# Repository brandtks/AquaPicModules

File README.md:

README
======
Board design and firmware for all modules used with the AquaPic Aquarium Controller. Each board should have corresponding firmware that works with that board version. All modules communicate with and are controlled by the [master controller/head unit](https://github.com/AquaPic/AquaPicController).

 * All PCB designs and layouts including gerber files are located under the _Boards_ directory. All PCB design is done using [KiCAD](http://kicad-pcb.org/). 
 * Firmware is located in the _Firmware_ directory. All the card's firmware should build without the need of the [MPLAB X IDE](http://www.microchip.com/mplab/mplab-x-ide), just the [XC compilers](http://www.microchip.com/mplab/compilers).
 * The _Documentation_ directory contains some useful information such as AquaPic Bus packets and other random notes.
 * Bill of materials are shared in [Google Drive](https://drive.google.com/drive/folders/1AOH0jgJ0CXvZnuD189EO4B9ZkvwggwkB?usp=sharing). 

### Status 
**IMPORTANT**: All modules are a work in progress. Most, if not all, are untested and very alpha quality.

### Website 
[HackADay Build Log](https://hackaday.io/project/1436-aquapic-aquarium-controller)

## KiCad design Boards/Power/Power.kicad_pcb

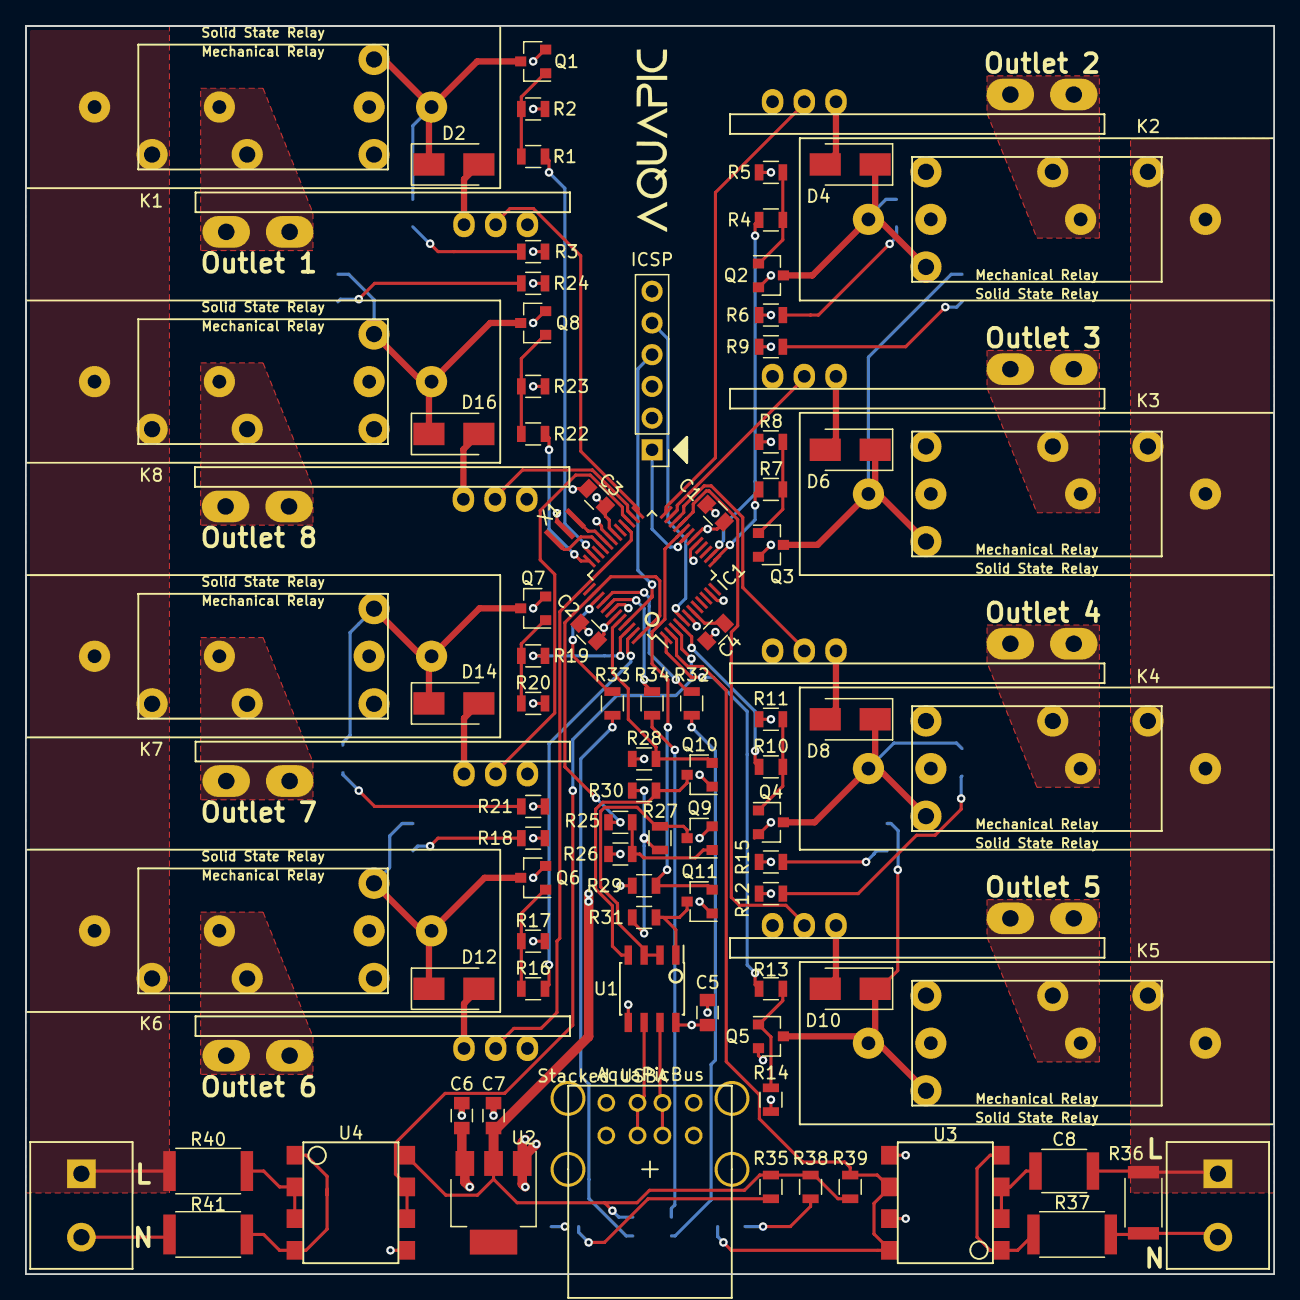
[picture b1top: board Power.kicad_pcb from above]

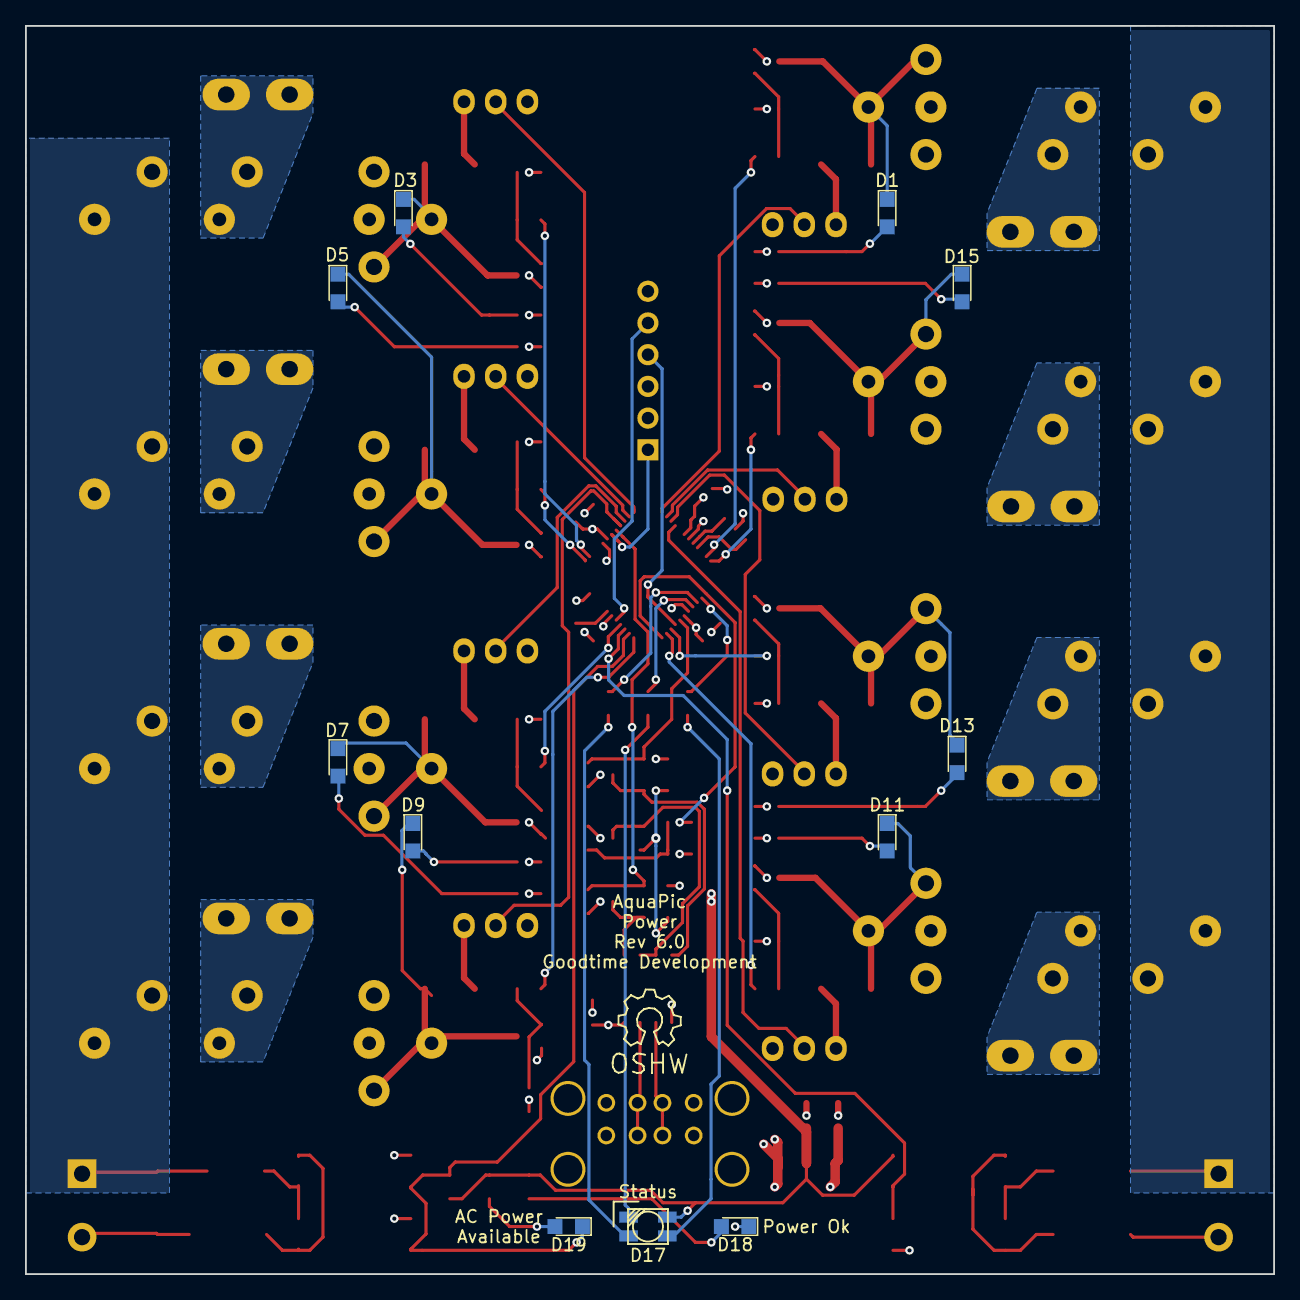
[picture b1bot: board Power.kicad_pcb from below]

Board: 4 copper layers, 100.0 x 100.0 mm, 105 parts (11 on the bottom side), 82 nets.

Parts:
C1, C2, C3, C4, C5: 100nF; C_0805
C6, C7: 4u7; C_0805
C8: 470nF; C_1812
D1, D3, D5, D7, D9, D11, D13, D15, D18, D19: APT2012; LED_0805
D2, D4, D6, D8, D10, D12, D14, D16: STPS130A; D_SMA
D17: SMTL4-RGY; PLCC-4
IC1: PIC32MM0064GPM048; TQFP-48_7x7mm_Pitch0.5mm
ICSP: 1x6 2.54 Pin Header; Pin_Header_Straight_1x06_Pitch2.54mm
K1, K2, K3, K4, K5, K6, K7, K8: Relay(Mech/SSR); Relay-Mech-SSR
P1, P2, P3, P4, P5, P6, P7, P8: Stab and 1x3; Current_Board
P11: Stacked USBA; USB-1.1_Stacked
P12, P13: 1x2 5.08; Screw_Header_1x2_5.08
Q1, Q2, Q3, Q4, Q5, Q6, Q7, Q8, Q9, Q10, Q11: NX7002AK; SOT-23
R1, R4, R7, R10, R13, R16, R19, R22, R25: 1K; R_0805
R2, R5, R8, R11, R14, R17, R20, R23, R26, R27, R39: 10K; R_0805
R3, R6, R9, R12, R15, R18, R21, R24: 100R; R_0805
R28, R29, R30, R31: 4K99; R_0805
R32, R33, R34, R35, R38: 150R; R_0805
R36: 1M; R_2010
R37: 1K; R_2512
R40, R41: 13K; R_2512
U1: ST485EC; SOIC-8_3.9x4.9mm_Pitch1.27mm
U2: AP2114H; SOT-223
U3, U4: LTV-826; 8_SMD_GULL_WING
X1: 8MHz; Resonator_3.2x1.3

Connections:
+3V3: C1.1, C2.1, C3.1, C7.1, D17.4, IC1.18, IC1.30, IC1.43, ICSP.2, Q10.1, Q11.1, R28.1, R29.1, R35.1, R38.2, R39.1, U2.2, U4.8
+5V: C5.1, C6.1, D2.2, D4.2, D6.2, D8.2, D10.2, D12.2, D14.2, D16.2, K1.3-1, K1.3-2, K2.3-1, K2.3-2, K3.3-1, K3.3-2, K4.3-1, K4.3-2, K5.3-1, K5.3-2, K6.3-1, K6.3-2, K7.3-1, K7.3-2, K8.3-1, K8.3-2, P1.2, P2.2, P3.2, P4.2, P5.2, P6.2, P7.2, P8.2, P11.1, P11.5, R3.1, R6.1, R9.1, R12.1, R15.1, R18.1, R21.1, R24.1, R27.1, R30.1, R31.1, U1.8, U2.3
//MCLR: IC1.19, ICSP.1
//RTS: IC1.38, IC1.48, R25.2
/A: P11.2, P11.6, U1.6
/AC_AVAIL: D19.1, IC1.2, R39.2, U3.6, U3.8
/B: P11.3, P11.7, U1.7
/CURRENT_1: IC1.25, P1.3
/CURRENT_2: IC1.24, P2.3
/CURRENT_3: IC1.23, P3.3
/CURRENT_4: IC1.22, P4.3
/CURRENT_5: IC1.21, P5.3
/CURRENT_6: IC1.28, P6.3
/CURRENT_7: IC1.27, P7.3
/CURRENT_8: IC1.26, P8.3
/L: C8.1, K1.1-1, K1.1-2, K2.1-1, K2.1-2, K3.1-1, K3.1-2, K4.1-1, K4.1-2, K5.1-1, K5.1-2, K6.1-1, K6.1-2, K7.1-1, K7.1-2, K8.1-1, K8.1-2, P12.1, P13.1, R36.2, R40.2
/L1: K1.2-1, K1.2-2, P1.1
/L2: K2.2-1, K2.2-2, P2.1
/L3: K3.2-1, K3.2-2, P3.1
/L4: K4.2-1, K4.2-2, P4.1
/L5: K5.2-1, K5.2-2, P5.1
/L6: K6.2-1, K6.2-2, P6.1
/L7: K7.2-1, K7.2-2, P7.1
/L8: K8.2-1, K8.2-2, P8.1
/LED_G: IC1.40, R32.2
/LED_R: IC1.41, R34.2
/LED_Y: IC1.39, R33.2
/N: P12.2, P13.2, R36.1, R37.1, R41.2
/PGC: IC1.5, ICSP.5
/PGD: IC1.45, ICSP.4
/RELAY_1: IC1.35, R1.2
/RELAY_2: IC1.14, R4.2
/RELAY_3: IC1.13, R7.2
/RELAY_4: IC1.4, R10.2
/RELAY_5: IC1.1, R13.2
/RELAY_6: IC1.47, R16.2
/RELAY_7: IC1.46, R19.2
/RELAY_8: IC1.36, R22.2
/RTS: Q9.3, R27.2, U1.2, U1.3
/RX: Q11.3, R31.2, U1.1
/RX_LV: IC1.20, Q11.2, R29.2
/TX: Q10.3, R30.2, U1.4
/TX_LV: IC1.44, Q10.2, R28.2
/ZERO_CROSS: IC1.3, U4.6, U4.7
GND: C1.2, C2.2, C3.2, C4.2, C5.2, C6.2, C7.2, D18.1, IC1.6, IC1.11, IC1.17, IC1.31, IC1.42, ICSP.3, P1.4, P2.4, P3.4, P4.4, P5.4, P6.4, P7.4, P8.4, P11.4, P11.8, Q1.2, Q2.2, Q3.2, Q4.2, Q5.2, Q6.2, Q7.2, Q8.2, Q9.2, R2.2, R5.2, R8.2, R11.2, R14.2, R17.2, R20.2, R23.2, R26.2, U1.5, U2.1, U3.5, U3.7, U4.5, X1.2
unnamed: C4.1, IC1.7
unnamed: C8.2, U3.2, U3.3
unnamed: D1.1, D2.1, K1.4-1, K1.4-2, Q1.3
unnamed: D1.2, R3.2
unnamed: D3.1, D4.1, K2.4-1, K2.4-2, Q2.3
unnamed: D3.2, R6.2
unnamed: D5.1, D6.1, K3.4-1, K3.4-2, Q3.3
unnamed: D5.2, R9.2
unnamed: D7.1, D8.1, K4.4-1, K4.4-2, Q4.3
unnamed: D7.2, R12.2
unnamed: D9.2, R15.2
unnamed: D9.1, D10.1, K5.4-1, K5.4-2, Q5.3
unnamed: D11.1, D12.1, K6.4-1, K6.4-2, Q6.3
unnamed: D11.2, R18.2
unnamed: D13.1, D14.1, K7.4-1, K7.4-2, Q7.3
unnamed: D13.2, R21.2
unnamed: D15.1, D16.1, K8.4-1, K8.4-2, Q8.3
unnamed: D15.2, R24.2
unnamed: D17.1, R32.1
unnamed: D17.2, R33.1
unnamed: D17.3, R34.1
unnamed: D18.2, R35.2
unnamed: D19.2, R38.1
unnamed: IC1.32, X1.3
unnamed: IC1.33, X1.1
unnamed: Q1.1, R1.1, R2.1
unnamed: Q2.1, R4.1, R5.1
unnamed: Q3.1, R7.1, R8.1
unnamed: Q4.1, R10.1, R11.1
unnamed: Q5.1, R13.1, R14.1
unnamed: Q6.1, R16.1, R17.1
unnamed: Q7.1, R19.1, R20.1
unnamed: Q8.1, R22.1, R23.1
unnamed: Q9.1, R25.1, R26.1
unnamed: R37.2, U3.1, U3.4
unnamed: R40.1, U4.2, U4.3
unnamed: R41.1, U4.1, U4.4

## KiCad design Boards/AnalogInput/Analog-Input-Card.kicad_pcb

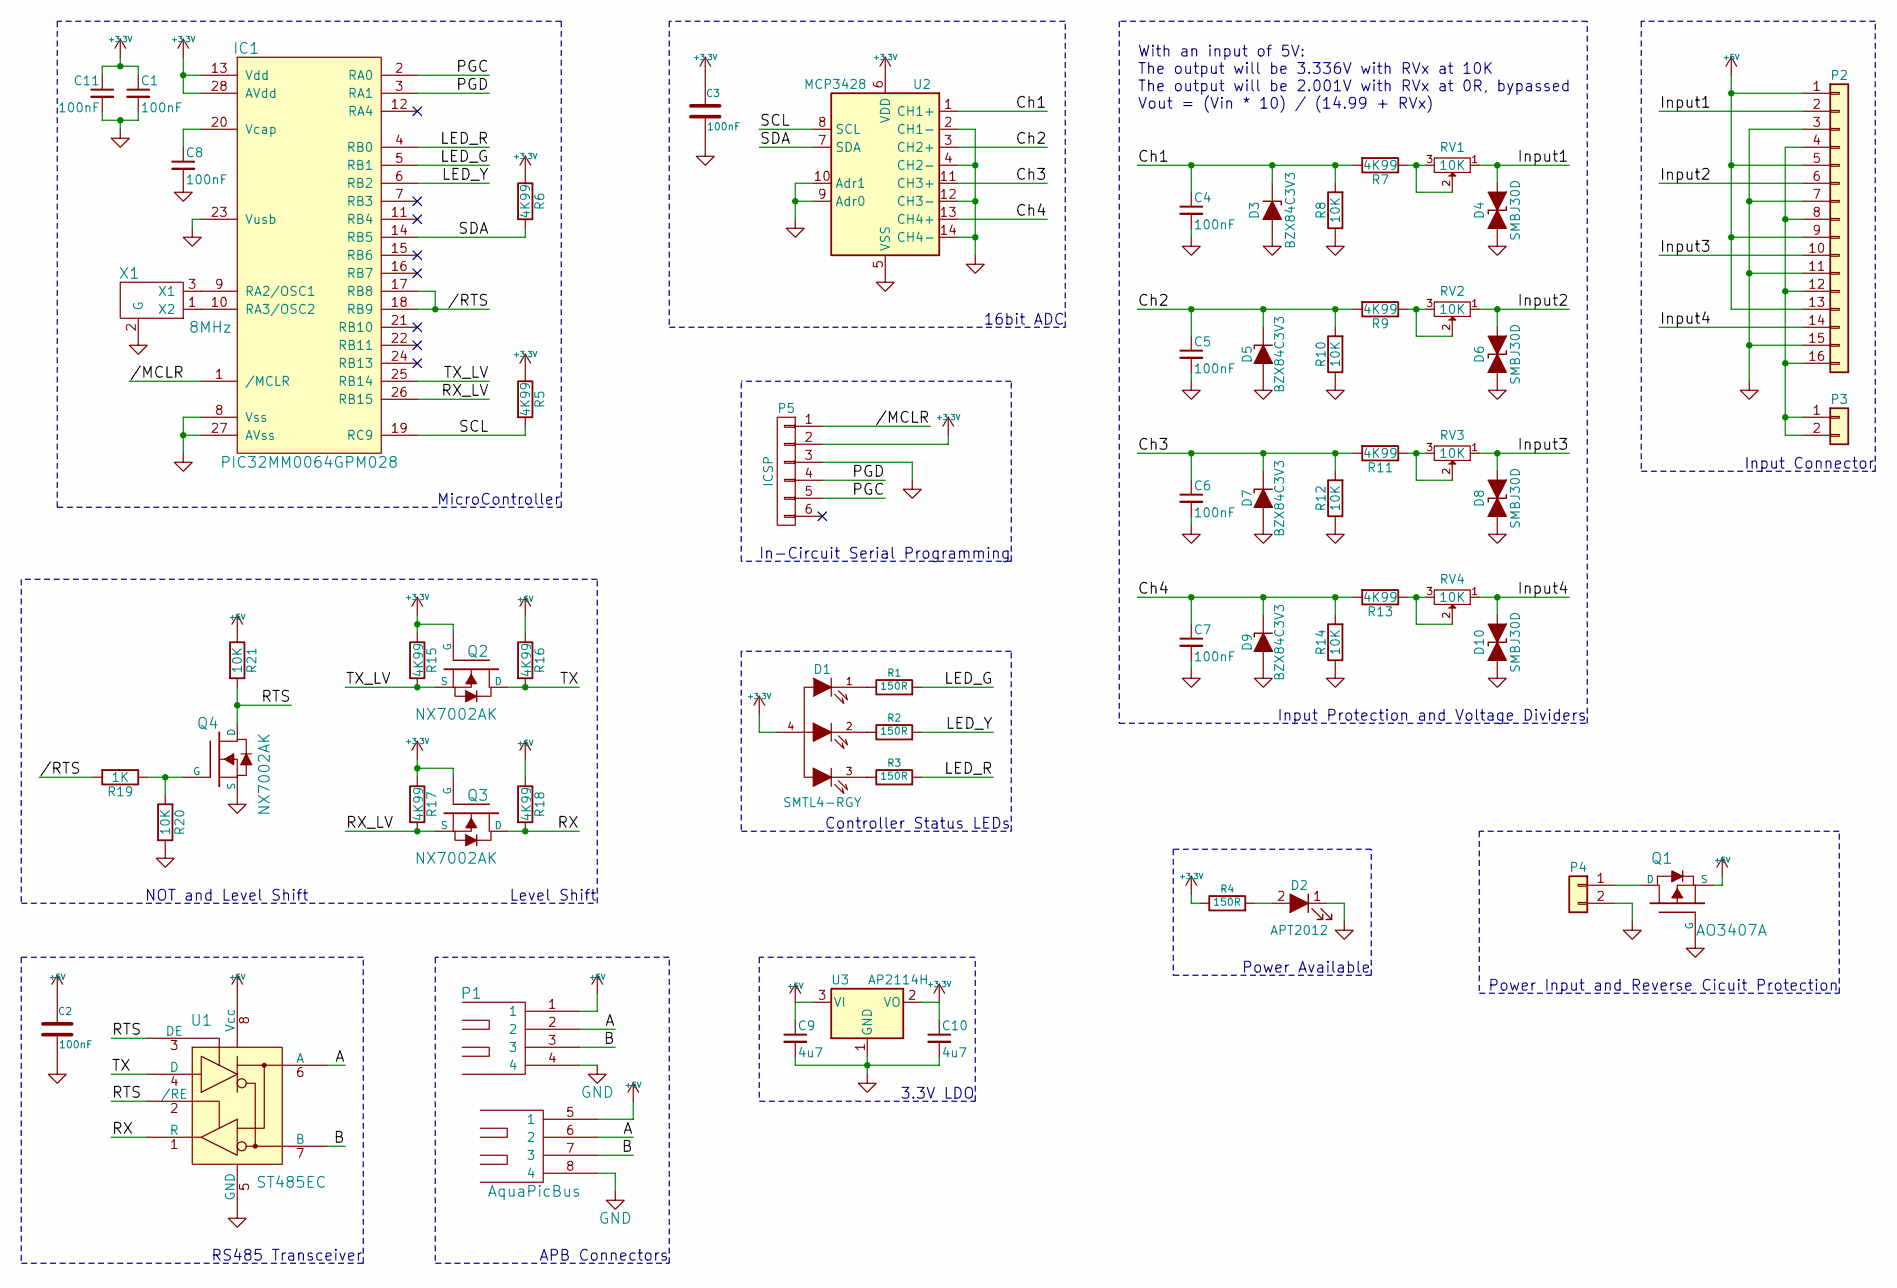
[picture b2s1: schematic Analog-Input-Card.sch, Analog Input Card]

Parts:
C1, C2, C3, C4, C5, C6, C7, C8, C11: 100nF; C_0805
C9, C10: 4u7; C_0805
D1: SMTL4-RGY; PLCC-4
D2: APT2012; LED-0805
D3, D5, D7, D9: BZX84C3V3; D_SOT-23_ANK
D4, D6, D8, D10: SMBJ30D; D_SMB
IC1: PIC32MM0064GPM028; SSOP-28_5.3x10.2mm_Pitch0.65mm
P1: AquaPicBus; USB-1.1_Stacked
P2: 1x16 2.54; Screw_Header_1x16
P3, P4: 1x2 2.54; Screw_Header_1x2
P5: ICSP; Pin_Header_Straight_1x06_Pitch2.54mm
Q1: AO3407A; SOT-23
Q2, Q3, Q4: NX7002AK; SOT-23
R1, R2, R3, R4: 150R; R_0805
R5, R6, R7, R9, R11, R13, R15, R16, R17, R18: 4K99; R_0805
R8, R10, R12, R14, R20, R21: 10K; R_0805
R19: 1K; R_0805
RV1, RV2, RV3, RV4: 10K; POTENTIAMETER_SMD
U1: ST485EC; SOIC-8_3.9x4.9mm_Pitch1.27mm
U2: MCP3428; TSSOP-14_4.4x5mm_Pitch0.65mm
U3: AP2114H; SOT-223
X1: 8MHz; Resonator_3.2x1.3

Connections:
+3V3: C1.1, C3.1, C10.1, C11.1, D1.4, IC1.13 (Vdd), IC1.28 (AVdd), P5.2, Q2.1 (G), Q3.1 (G), R4.1, R5.1, R6.1, R15.1, R17.1, U2.6 (VDD), U3.2 (VO); also elsewhere on the board
+5V: C2.1, C9.1, P1.1, P1.5 (1), P2.1, P2.5, P2.9, P2.13, Q1.2 (S), R16.1, R18.1, R21.1, U1.8 (Vcc), U3.3 (VI)
//MCLR: IC1.1 (/MCLR), P5.1; also elsewhere on the board
//RTS: IC1.17 (RB8), IC1.18 (RB9), R19.2
/A: P1.2, P1.6 (2), U1.6 (A)
/B: P1.3, P1.7 (3), U1.7 (B)
/Ch1: C4.1, D3.1 (K), R7.2, R8.2, U2.1 (CH1+)
/Ch2: C5.1, D5.1 (K), R9.2, R10.2, U2.3 (CH2+)
/Ch3: C6.1, D7.1 (K), R11.2, R12.2, U2.11 (CH3+)
/Ch4: C7.1, D9.1 (K), R13.2, R14.2, U2.13 (CH4+)
/Input1: D4.1 (A1), P2.2, RV1.1
/Input2: D6.1 (A1), P2.6, RV2.1
/Input3: D8.1 (A1), P2.10, RV3.1
/Input4: D10.1 (A1), P2.14, RV4.1
/LED_G: IC1.5 (RB1), R1.2
/LED_R: IC1.4 (RB0), R3.2
/LED_Y: IC1.6 (RB2), R2.2
/PGC: IC1.2 (RA0), P5.5; also elsewhere on the board
/PGD: IC1.3 (RA1), P5.4; also elsewhere on the board
/RTS: Q4.3 (D), R21.2, U1.2 (/RE), U1.3 (DE)
/RX: Q3.3 (D), R18.2, U1.1 (R)
/RX_LV: IC1.26 (RB15), Q3.2 (S), R17.2
/SCL: IC1.19 (RC9), R5.2, U2.8 (SCL)
/SDA: IC1.14 (RB5), R6.2, U2.7 (SDA)
/TX: Q2.3 (D), R16.2, U1.4 (D)
/TX_LV: IC1.25 (RB14), Q2.2 (S), R15.2
GND: C1.2, C2.2, C3.2, C4.2, C5.2, C6.2, C7.2, C8.2, C9.2, C10.2, C11.2, D2.1 (K), D3.2 (A), D4.2 (A2), D5.2 (A), D6.2 (A2), D7.2 (A), D8.2 (A2), D9.2 (A), D10.2 (A2), IC1.8 (Vss), IC1.23 (Vusb), IC1.27 (AVss), P1.4, P1.8 (4), P2.3, P2.7, P2.11, P2.15, P4.2, P5.3, Q1.1 (G), Q4.2 (S), R8.1, R10.1, R12.1, R14.1, R20.2, U1.5 (GND), U2.2 (CH1-), U2.4 (CH2-), U2.5 (VSS), U2.9 (Adr0), U2.10 (Adr1), U2.12 (CH3-), U2.14 (CH4-), U3.1 (GND), X1.2 (G); also elsewhere on the board
unnamed: C8.1, IC1.20 (Vcap)
unnamed: D1.1, R1.1
unnamed: D1.2, R2.1
unnamed: D1.3, R3.1
unnamed: D2.2 (A), R4.2
unnamed: IC1.9 (RA2/OSC1), X1.3 (X1)
unnamed: IC1.10 (RA3/OSC2), X1.1 (X2)
unnamed: P2.4, P2.8, P2.12, P2.16, P3.1, P3.2
unnamed 43: P4.1, Q1.3 (D); also elsewhere on the board
unnamed: Q4.1 (G), R19.1, R20.1
unnamed: R7.1, RV1.2, RV1.3
unnamed: R9.1, RV2.2, RV2.3
unnamed: R11.1, RV3.2, RV3.3
unnamed: R13.1, RV4.2, RV4.3

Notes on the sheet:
In-Circuit Serial Programming
MicroController
Input Connector
RS485 Transceiver
Power Input and Reverse Cicuit Protection
APB Connectors
16bit ADC
Input Protection and Voltage Dividers
With an input of 5V: The output will be 3.336V with RVx at 10K The output will be 2.001V with RVx at 0R, bypassed Vout = (Vin * 10) / (14.99 + RVx)
Level Shift
NOT and Level Shift
3.3V LDO
Controller Status LEDs
Power Available

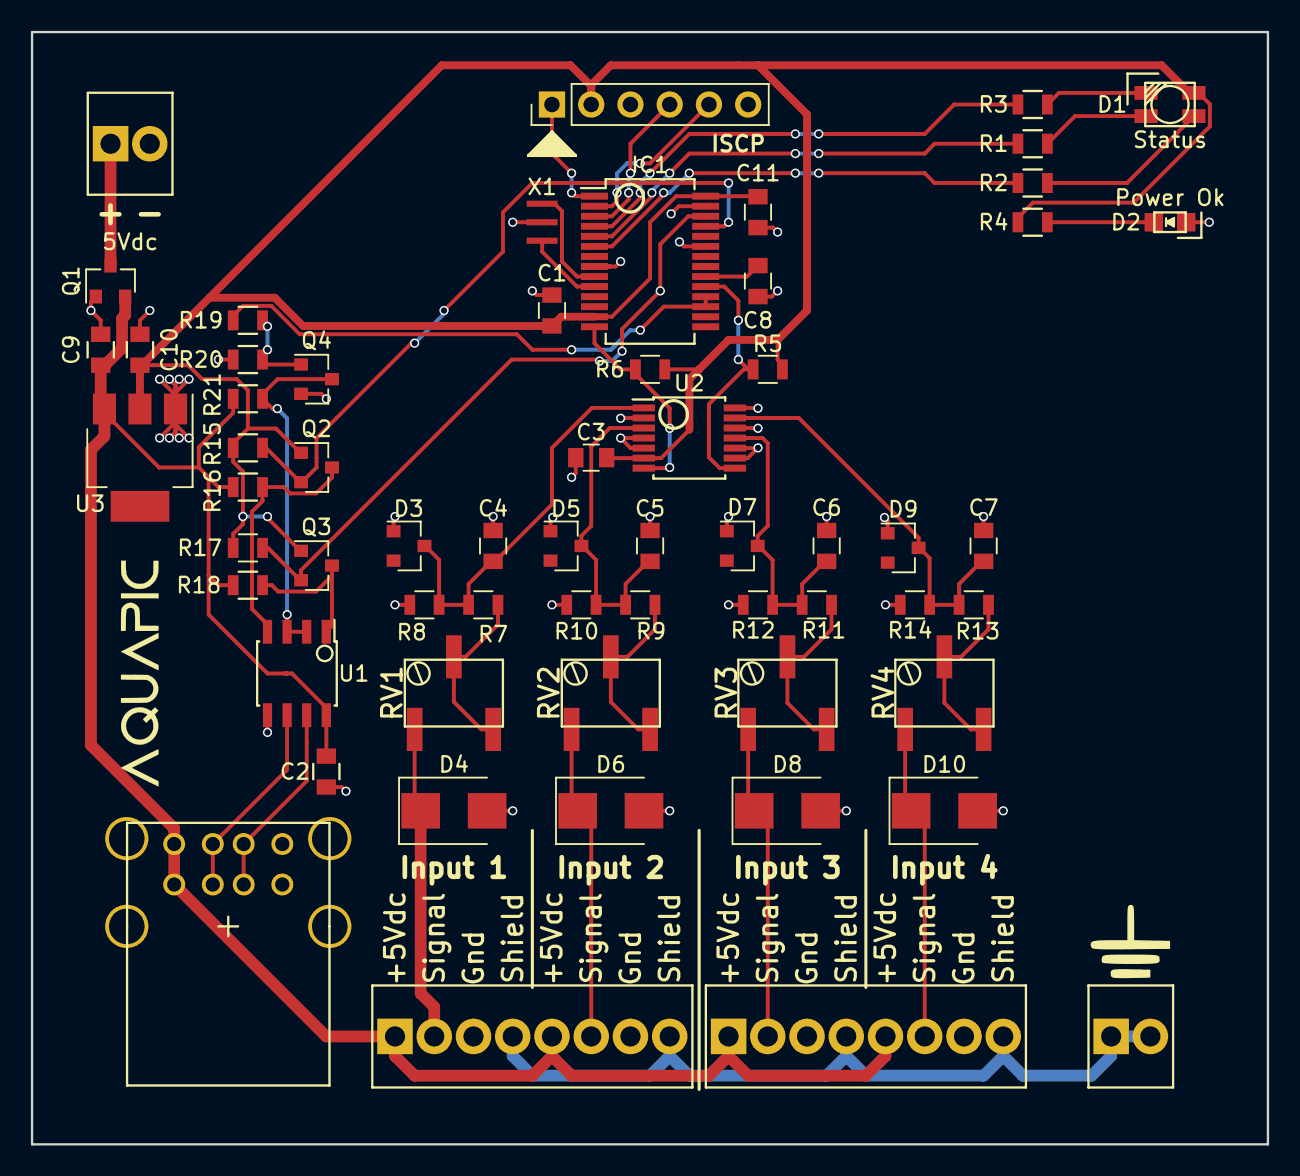
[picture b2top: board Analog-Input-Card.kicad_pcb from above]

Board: 2 copper layers, 80.0 x 72.0 mm, 60 parts (0 on the bottom side), 41 nets.

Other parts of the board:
5Vdc: 2x1 2.54; Screw_Header_1x2
P1#2: 6x1 2.54; Pin_Header_Straight_1x06_Pitch2.54mm

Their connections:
+3V3: P1#2.2; also elsewhere on the board
//MCLR: P1#2.1; also elsewhere on the board
/PGC: P1#2.5; also elsewhere on the board
/PGD: P1#2.4; also elsewhere on the board
GND: 5Vdc.2, P1#2.3; also elsewhere on the board
unnamed 43: 5Vdc.1; also elsewhere on the board

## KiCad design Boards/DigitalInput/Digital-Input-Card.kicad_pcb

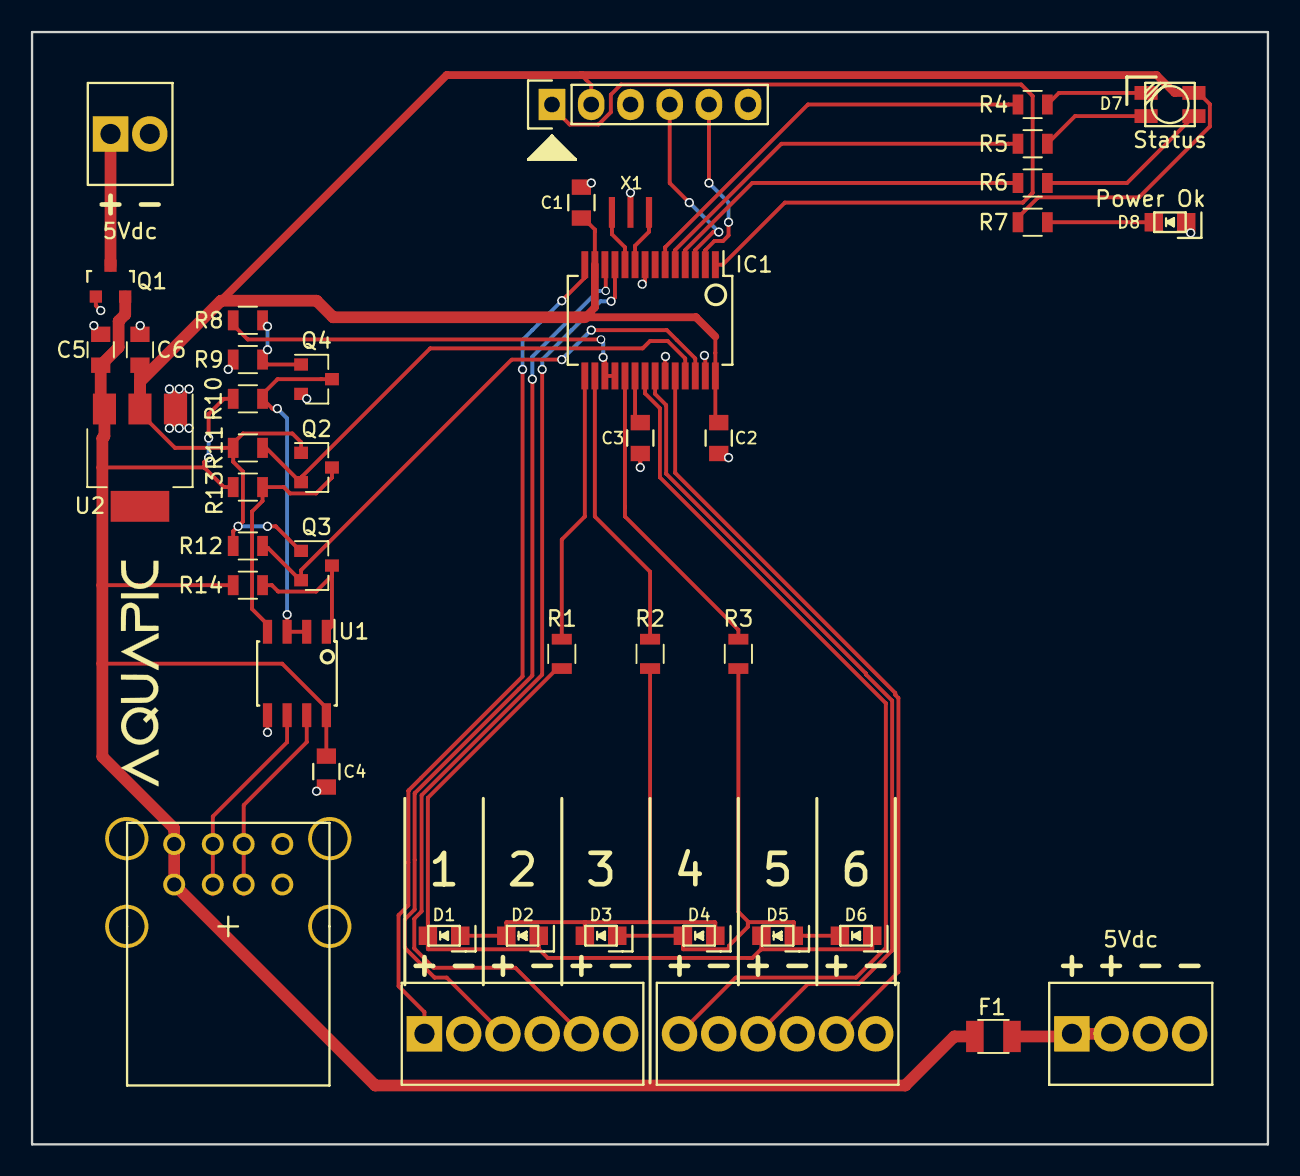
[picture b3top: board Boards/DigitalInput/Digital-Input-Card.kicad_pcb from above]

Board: 2 copper layers, 80.0 x 72.0 mm, 42 parts (0 on the bottom side), 39 nets.

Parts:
C1, C2, C3, C4: 100nF; C_0805
C5, C6: 4u7; C_0805
D1, D2, D3, D4, D5, D6, D8: APT2012; LED-0805
D7: SMTL4-RGY; PLCC-4
F1: 750mA; Fuse_SMD1206_Reflow
IC1: PIC32MM0064GPM028; SSOP-28_5.3x10.2mm_Pitch0.65mm
P1: 1x6 2.54 Pin Header; Pin_Header_Straight_1x06
P2: 1x12 2.54; Screw_Header_1x12
P3: 1x2 2.54; Screw_Header_1x2
P4: 1x4 2.54; Screw_Header_1x4
P5: Stacked USBA; USB-1.1_Stacked
Q1: AO3407A; SOT-23
Q2, Q3, Q4: NX7002AK; SOT-23
R1, R2, R3: 20R; R_0805
R4, R5, R6, R7: 150R; R_0805
R8: 1K; R_0805
R9, R10: 10K; R_0805
R11, R12, R13, R14: 4K99; R_0805
U1: ST485EC; SOIC-8_3.9x4.9mm_Pitch1.27mm
U2: AP2114H; SOT-223
X1: 8MHz; Resonator_3.2x1.3

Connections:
+3V3: C1.1, C2.1, C6.1, D7.4, IC1.13, IC1.28, P1.2, Q2.1, Q3.1, R7.1, R11.1, R12.1, U2.2
+5V: C4.1, C5.1, F1.1, P5.1, P5.5, Q1.2, R10.1, R13.1, R14.1, U1.8, U2.3
//MCLR: IC1.1, P1.1
//RTS: IC1.17, IC1.18, R8.2
/A: P5.2, P5.6, U1.6
/B: P5.3, P5.7, U1.7
/Input1: IC1.14, P2.1
/Input2: IC1.12, P2.3
/Input3: IC1.11, P2.5
/Input4: IC1.21, P2.7
/Input5: IC1.22, P2.9
/Input6: IC1.24, P2.11
/LED1: IC1.15, R1.1
/LED2: IC1.16, R2.1
/LED3: IC1.19, R3.1
/LED_G: IC1.5, R5.2
/LED_R: IC1.6, R4.2
/LED_Y: IC1.4, R6.2
/PGC: IC1.2, P1.5
/PGD: IC1.3, P1.4
/RTS: Q4.3, R10.2, U1.2, U1.3
/RX: Q3.3, R14.2, U1.1
/RX_LV: IC1.26, Q3.2, R12.2
/TX: Q2.3, R13.2, U1.4
/TX_LV: IC1.25, Q2.2, R11.2
GND: C1.2, C2.2, C3.2, C4.2, C5.2, C6.2, D8.1, IC1.8, IC1.23, IC1.27, P1.3, P2.2, P2.4, P2.6, P2.8, P2.10, P2.12, P3.2, P4.3, P4.4, P5.4, P5.8, Q1.1, Q4.2, R9.2, U1.5, U2.1, X1.2
unnamed: C3.1, IC1.20
unnamed: D1.1, D2.2, D3.2, D4.1, R2.2
unnamed: D1.2, D2.1, D5.2, D6.1, R1.2
unnamed: D3.1, D4.2, D5.1, D6.2, R3.2
unnamed: D7.1, R5.1
unnamed: D7.2, R6.1
unnamed: D7.3, R4.1
unnamed: D8.2, R7.2
unnamed: F1.2, P4.1, P4.2
unnamed: IC1.9, X1.3
unnamed: IC1.10, X1.1
unnamed: P3.1, Q1.3
unnamed: Q4.1, R8.1, R9.1

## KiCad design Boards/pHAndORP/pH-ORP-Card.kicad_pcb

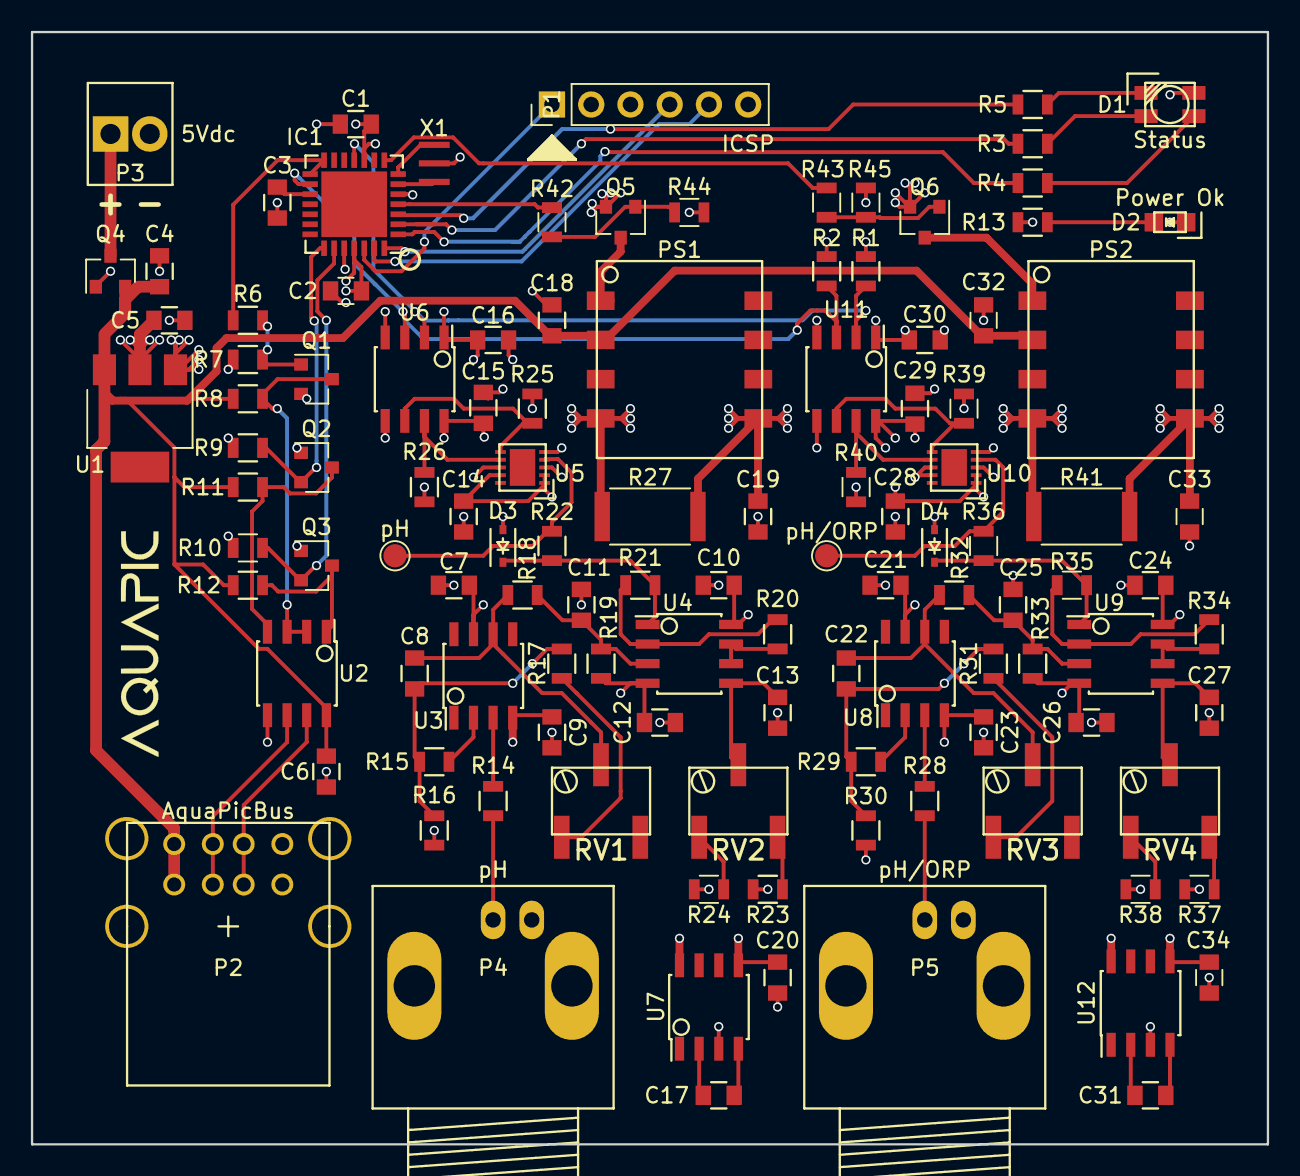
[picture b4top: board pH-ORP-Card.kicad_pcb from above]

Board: 4 copper layers, 80.0 x 72.0 mm, 116 parts (0 on the bottom side), 76 nets.

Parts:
C1, C2, C3, C6, C7, C9, C10, C11, C12, C14, C15, C16, C21, C23, C24, C25, C26, C28, C29, C30: 100nF; C_0805
C4, C5, C18, C32: 4u7; C_0805
C8, C22: 33pF; C_0805
C13, C27: 1uF; C_0805
C17, C19, C20, C31, C33, C34: 10uF; C_0805
D1: SMTL4-RGY; PLCC-4
D2: APT2012; LED-0805
D3, D4: DB2J310; SOD-323
IC1: PIC32MM0064GPM028; QFN-28-1EP_6x6mm_Pitch0.65mm
P1: ICSP; PinHeader_1x06_P2.54mm_Vertical
P2: AquaPicBus; USB-1.1_Stacked
P3: 5Vdc; Screw_Header_1x2
P4: pH; BNC_Socket_TYCO-AMP_LargePads
P5: pH/ORP; BNC_Socket_TYCO-AMP_LargePads
PS1, PS2: R1SE-0505; 8-SMD
Q1, Q2, Q3, Q5, Q6: NX7002AK; SOT-23
Q4: AO3407A; SOT-23
R1, R2, R9, R10, R11, R12, R25, R26, R39, R40: 4K99; R_0805
R3, R4, R5, R13: 150R; R_0805
R6, R22, R36, R42, R43: 1K; R_0805
R7, R8, R14, R23, R24, R28, R37, R38, R44, R45: 10K; R_0805
R15, R29: 2M; R_0805
R16: 49K9; R_0805
R17, R18, R19, R20, R21, R31, R32, R33, R34, R35: 221K; R_0805
R27, R41: 50R; R_2512
R30: 100K; R_0805
RV1, RV3: 50K; POTENTIAMETER_SMD
RV2, RV4: 10K; POTENTIAMETER_SMD
TP1: pH; TestPoint_Pad_D1.5mm
TP2: pH/ORP; TestPoint_Pad_D1.5mm
U1: AP2114H; SOT-223
U2: ST485EC; SOIC-8_3.9x4.9mm_Pitch1.27mm
U3, U8: LMC6061; SOIC-8_3.9x4.9mm_Pitch1.27mm
U4, U9: TLV272; SOIC-8_3.9x4.9mm_Pitch1.27mm
U5, U10: LTC2483; DFN-10_3x3mm
U6, U11: Si8602; SOIC-8_3.9x4.9mm_Pitch1.27mm
U7, U12: TC7660; SOIC-8_3.9x4.9mm_Pitch1.27mm
X1: 8MHz; Resonator_3.2x1.3

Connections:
+3V3: C1.1, C2.1, C5.1, C16.1, C30.1, D1.4, IC1.10, IC1.25, P1.2, Q2.1, Q3.1, R1.1, R2.1, R9.1, R10.1, R13.1, U1.2, U6.1, U11.1
+5V: C4.1, C6.1, C18.1, C32.1, P2.1, P2.5, PS1.2, PS2.2, Q4.2, R8.1, R11.1, R12.1, U1.3, U2.8
+5VA: C21.1, C24.1, C28.1, C29.1, C33.1, PS2.5, R39.1, R40.1, R41.1, U8.7, U9.8, U10.1, U10.2, U11.8, U12.8
+5VD: C7.1, C10.1, C14.1, C15.1, C19.1, PS1.5, R25.1, R26.1, R27.1, U3.7, U4.8, U5.1, U5.2, U5.9, U6.8, U7.8
-5V: C9.2, C11.2, C12.2, C20.2, R19.2, R24.2, U3.4, U4.4, U7.5
-5VA: C23.2, C25.2, C26.2, C34.2, R33.2, R38.2, U8.4, U9.4, U12.5
//MCLR: IC1.26, P1.1
//RTS: IC1.14, IC1.15, R6.2
/A: P2.2, P2.6, U2.6
/A_pH: R22.2, TP1.1, U5.4
/A_pH/ORP: R36.2, TP2.1, U10.4
/B: P2.3, P2.7, U2.7
/En_pH: IC1.4, R42.2
/En_pH/ORP: IC1.8, R43.2
/LED_G: IC1.2, R3.2
/LED_R: IC1.3, R5.2
/LED_Y: IC1.1, R4.2
/PGC: IC1.27, P1.5
/PGD: IC1.28, P1.4
/RTS: Q1.3, R8.2, U2.2, U2.3
/RX: Q3.3, R12.2, U2.1
/RX_LV: IC1.23, Q3.2, R10.2
/SCL: IC1.16, R2.2, U6.3, U11.3
/SDA: IC1.11, R1.2, U6.2, U11.2
/TX: Q2.3, R11.2, U2.4
/TX_LV: IC1.22, Q2.2, R9.2
GND: C1.2, C2.2, C3.2, C4.2, C5.2, C6.2, C16.2, C18.2, C30.2, C32.2, D2.1, IC1.5, IC1.24, P1.3, P2.4, P2.8, P3.2, Q1.2, Q4.1, Q5.2, Q6.2, R7.2, R44.2, R45.2, U1.1, U2.5, U6.4, U11.4, X1.2
GNDA: C21.2, C23.1, C24.2, C26.1, C27.1, C28.2, C29.2, C33.2, C34.1, D4.2, P5.2, PS2.4, R30.2, R37.1, R41.2, U10.3, U10.5, U10.8, U10.9, U11.5, U12.3
GNDD: C7.2, C9.1, C10.2, C12.1, C13.1, C14.2, C15.2, C19.2, C20.1, D3.2, P4.2, PS1.4, R16.2, R23.1, R27.2, U5.3, U5.5, U5.8, U6.5, U7.3
unnamed: C3.1, IC1.17
unnamed: C8.1, R15.2, R16.1, R17.1
unnamed: C8.2, R18.1, RV1.2, U3.6
unnamed: C11.1, R18.2, R19.1, U4.3
unnamed: C13.2, RV2.2, U4.5
unnamed: C17.1, U7.2
unnamed: C17.2, U7.4
unnamed: PS1.1, Q5.3
unnamed: C22.1, R29.2, R30.1, R31.1
unnamed: C22.2, R32.1, RV3.2, U8.6
unnamed: C25.1, R32.2, R33.1, U9.3
unnamed: C27.2, RV4.2, U9.5
unnamed: C31.1, U12.2
unnamed: C31.2, U12.4
unnamed: PS2.1, Q6.3
unnamed: D1.1, R3.1
unnamed: D1.2, R4.1
unnamed: D1.3, R5.1
unnamed: D2.2, R13.2
unnamed: D3.1, R21.2, R22.1, U4.1
unnamed: D4.1, R35.2, R36.1, U9.1
unnamed: IC1.6, X1.3
unnamed: IC1.7, X1.1
unnamed: P3.1, Q4.3
unnamed: P4.1, R14.1
unnamed: P5.1, R28.1
unnamed: Q1.1, R6.1, R7.1
unnamed: Q5.1, R42.1, R44.1
unnamed: Q6.1, R43.1, R45.1
unnamed: R14.2, U3.3
unnamed: R15.1, U3.2
unnamed: R17.2, RV1.1
unnamed: R20.1, R21.1, U4.2
unnamed: R20.2, U4.6, U4.7
unnamed: R23.2, RV2.3
unnamed: R24.1, RV2.1
unnamed: R25.2, U5.6, U6.6
unnamed: R26.2, U5.7, U6.7
unnamed: R28.2, U8.3
unnamed: R29.1, U8.2
unnamed: R31.2, RV3.1
unnamed: R34.1, R35.1, U9.2
unnamed: R34.2, U9.6, U9.7
unnamed: R37.2, RV4.3
unnamed: R38.1, RV4.1
unnamed: R39.2, U10.6, U11.6
unnamed: R40.2, U10.7, U11.7

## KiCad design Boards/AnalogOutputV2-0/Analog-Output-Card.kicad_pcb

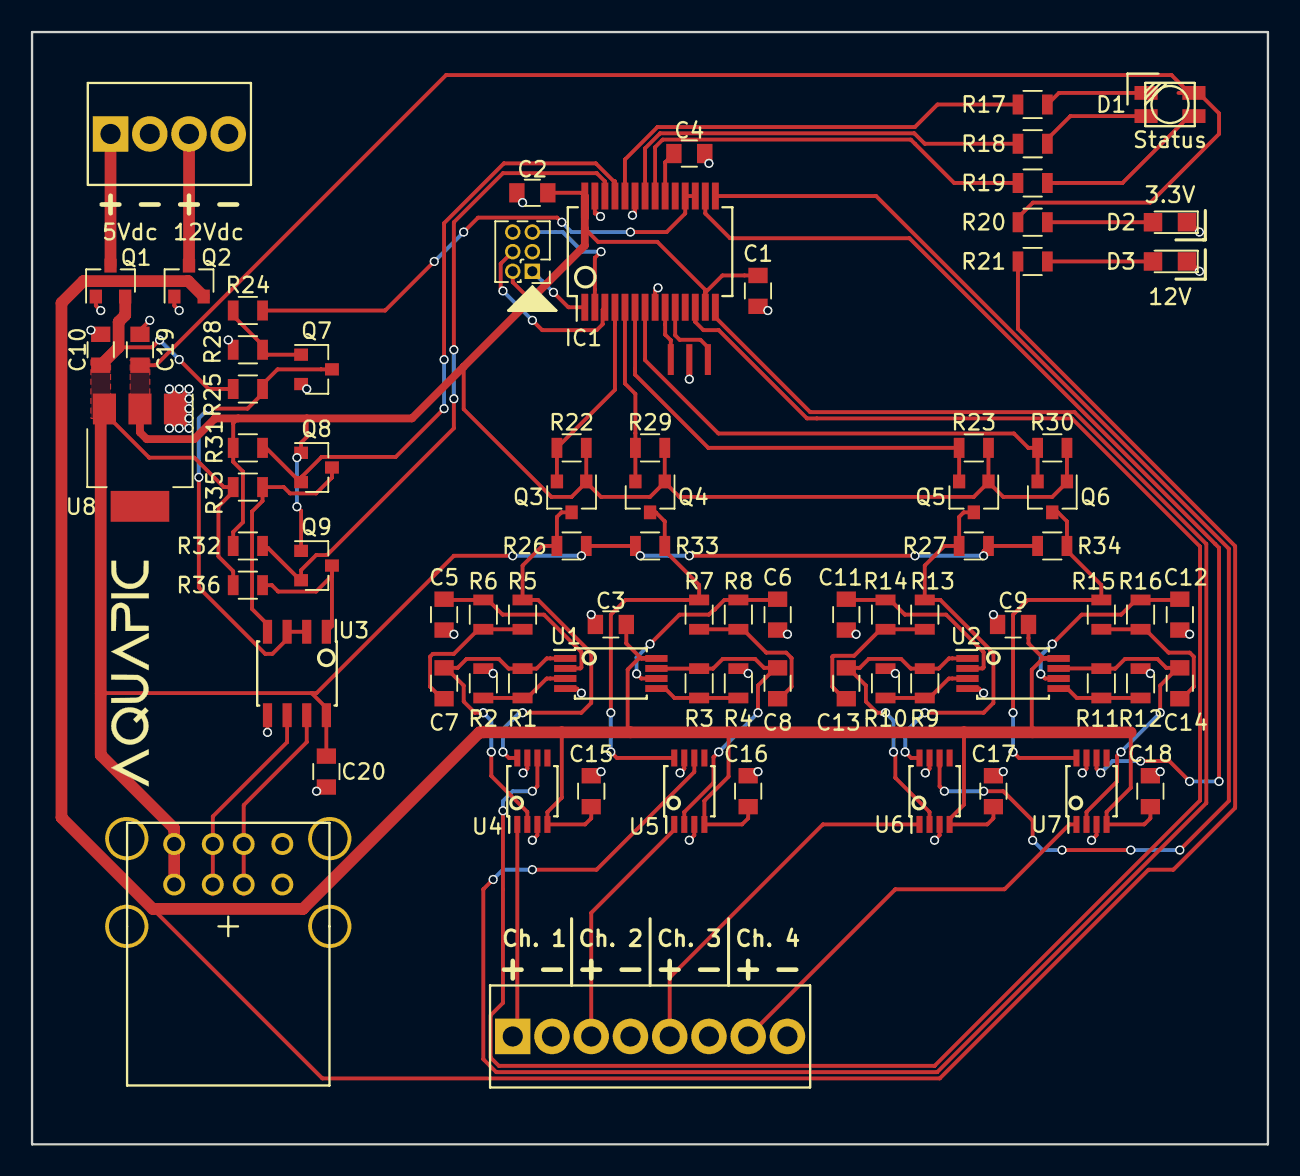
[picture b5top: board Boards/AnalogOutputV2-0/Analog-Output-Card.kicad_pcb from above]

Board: 2 copper layers, 80.0 x 72.0 mm, 82 parts (0 on the bottom side), 61 nets.

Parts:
C1, C2, C3, C4, C7, C8, C9, C13, C14, C15, C16, C17, C18, C20: 100nF; C_0805
C5, C6, C11, C12: 220nF; C_0805
C10, C19: 4u7; C_0805
D1: SMTL4-RGY; PLCC-4
D2, D3: APT2012; LED_0805
IC1: PIC32MM0064GPM028; SSOP-28_5.3x10.2mm_Pitch0.65mm
P1: 8x1 2.54; Screw_Header_1x8
P2: Stacked USBA; USB-1.1_Stacked
P3: 4x1 2.54; Screw_Header_1x4
P4: 6x1 2.54 Pin Header; Pin_Header_Straight_2x03_Pitch1.27mm
Q1, Q2: AO3407A; SOT-23
Q3, Q4, Q5, Q6, Q7, Q8, Q9: NX7002AK; SOT-23
R1, R2, R3, R4, R6, R8, R9, R10, R11, R12, R14, R16, R25, R28: 10K; R_0805
R5, R7, R13, R15: 100K; R_0805
R17, R18, R19, R20: 150R; R_0805
R21, R24: 1K; R_0805
R22, R23, R26, R27, R29, R30, R31, R32, R33, R34, R35, R36: 4K99; R_0805
U1, U2: LM358; TSSOP-8_4.4x3mm_Pitch0.65mm
U3: ST485EC; SOIC-8_3.9x4.9mm_Pitch1.27mm
U4, U5, U6, U7: DG469; TSSOP-8_3x3mm_Pitch0.65mm
U8: AP2114H; SOT-223
X1: 8MHz; Resonator_3.2x1.3

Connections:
+3V3: C1.1, C2.1, C19.1, D1.4, IC1.13, IC1.28, P4.2, Q3.1, Q4.1, Q5.1, Q6.1, Q8.1, Q9.1, R20.1, R22.1, R23.1, R29.1, R30.1, R31.1, R32.1, U8.2
+5V: C10.1, C20.1, P2.1, P2.5, Q1.2, R26.1, R27.1, R28.1, R33.1, R34.1, R35.1, R36.1, U3.8, U8.3
+12V: C3.1, C9.1, C15.1, C16.1, C17.1, C18.1, Q2.2, R21.1, U1.8, U2.8, U4.4, U5.4, U6.4, U7.4
//MCLR: IC1.1, P4.1
//RTS: IC1.17, IC1.18, R24.2
/A: P2.2, P2.6, U3.6
/A1: C7.2, R1.2, U1.1, U4.2
/A2: C8.2, R3.2, U1.7, U5.2
/A3: C13.2, R9.2, U2.1, U6.2
/A4: C14.2, R11.2, U2.7, U7.2
/B: P2.3, P2.7, U3.7
/LED_G: IC1.22, R18.2
/LED_R: IC1.24, R17.2
/LED_Y: IC1.21, R19.2
/OUT1: P1.1, U4.1
/OUT2: P1.3, U5.1
/OUT3: P1.5, U6.1
/OUT4: P1.7, U7.1
/PGC: IC1.2, P4.5
/PGD: IC1.3, P4.4
/PWM1: Q3.3, R5.1, R26.2, U4.8
/PWM1_LV: IC1.4, Q3.2, R22.2
/PWM2: Q4.3, R7.1, R33.2, U5.8
/PWM2_LV: IC1.5, Q4.2, R29.2
/PWM3: Q5.3, R13.1, R27.2, U6.8
/PWM3_LV: IC1.6, Q5.2, R23.2
/PWM4: Q6.3, R15.1, R34.2, U7.8
/PWM4_LV: IC1.7, Q6.2, R30.2
/RELAY1: IC1.12, U4.6
/RELAY2: IC1.14, U5.6
/RELAY3: IC1.15, U6.6
/RELAY4: IC1.16, U7.6
/RTS: Q7.3, R28.2, U3.2, U3.3
/RX: Q9.3, R36.2, U3.1
/RX_LV: IC1.26, Q9.2, R32.2
/TX: Q8.3, R35.2, U3.4
/TX_LV: IC1.25, Q8.2, R31.2
GND: C1.2, C2.2, C3.2, C4.2, C5.2, C6.2, C9.2, C10.2, C11.2, C12.2, C15.2, C16.2, C17.2, C18.2, C19.2, C20.2, D2.1, D3.1, IC1.8, IC1.23, IC1.27, P1.2, P1.4, P1.6, P1.8, P2.4, P2.8, P3.2, P3.4, P4.3, Q1.1, Q2.1, Q7.2, R2.2, R4.2, R10.2, R12.2, R25.2, U1.4, U2.4, U3.5, U4.3, U4.7, U5.3, U5.7, U6.3, U6.7, U7.3, U7.7, U8.1, X1.2
unnamed: C4.1, IC1.20
unnamed: C5.1, R6.2, U1.2
unnamed: C6.1, R8.2, U1.6
unnamed: C7.1, R5.2, R6.1
unnamed: C8.1, R7.2, R8.1
unnamed: C11.1, R14.2, U2.2
unnamed: C12.1, R16.2, U2.6
unnamed: C13.1, R13.2, R14.1
unnamed: C14.1, R15.2, R16.1
unnamed: D1.1, R18.1
unnamed: D1.2, R19.1
unnamed: D1.3, R17.1
unnamed: D2.2, R20.2
unnamed: D3.2, R21.2
unnamed: IC1.9, X1.3
unnamed: IC1.10, X1.1
unnamed: P3.1, Q1.3
unnamed: P3.3, Q2.3
unnamed: Q7.1, R24.1, R25.1
unnamed: R1.1, R2.1, U1.3
unnamed: R3.1, R4.1, U1.5
unnamed: R9.1, R10.1, U2.3
unnamed: R11.1, R12.1, U2.5

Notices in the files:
Firmware/projects/Power.X/mcc_generated_files/pin_manager.h:
Copyright (c) 2013 - 2015 released Microchip Technology Inc.  All rights reserved.
